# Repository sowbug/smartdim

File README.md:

SmartDim
===

A timed dimmer for the Ikea JANSJÖ lamp. Using pulse-width modulation, it starts the light at full brightness, waits 30 minutes, then dims gradually to full darkness over 5 minutes. In theory it's good for a kid who wakes up when the parent comes back in to shut off the reading light.

Parts List
===

* One [Ikea JANSJÖ clip lamp](http://www.ikea.com/us/en/catalog/products/30237256/#/20315674). The one I got was item 801.696.36 and it was marked down to $12.99. If it has a 2-pin DIN speaker connector for the power adapter, and the power is 4 volts at 0.75 amps (3 watts), then it ought to work with this project. Be careful and check the voltage. I've seen other lamps in the JANSJÖ series that run on 7 volts, and that voltage will kill this circuit.
* A way to manufacture PCBs. You will, of course, use [OSH Park](https://oshpark.com/).
* Any old N-channel MOSFET in SOT-223 package that can handle a couple of amps. I used the [NDT3055L](https://www.jameco.com/webapp/wcs/stores/servlet/Product_10001_10001_874875_-1), which says it can dissipate 3 watts. I'd have preferred something with more margin for error, but this was available at Jameco will-call.
* An ATTiny85-20SU, which is the SOIC-8 package. Depending on how lazy you are, you can pick a smaller version of this series and figure out how to scrunch down the firmware size.
* A 6-pin AVR ISP.
* Either a [ProtoProg](http://protofusion.org/wordpress/2013/05/open-hardware-pogo-pin-programmer/) connector or an SOIC-8 clip to program the t85. Yeah, I probably could have fit a standard 6-pin header on this board. Sorry about that.
* An 0805 1uF capacitor.
* The standard [Dangerous Prototypes octagon-shaped SMD button](http://dangerousprototypes.com/docs/Partlist#Buttons_and_switches) (ALPS SKQGAKE010) (note the KE010 variant, which has a 3.43N rather than 2.55N operating force, but which is 50 cents cheaper). I usually use the [TD-85XU](http://www.dx.com/p/td-85xu-mini-tact-switches-50-piece-pack-122514#.VmRq-H4rKV4) because you can acquire a lifetime supply for $10, but I wanted something that was easier to find in the dark, and I happened to have some left over from another project. Looking back (to a few hours ago when this project started), I probably should have picked something a little less premium and with even more travel ([take your pick](http://www.dx.com/s/tact+switch)).
* Depending on whether you want to cut the lamp wires, a male and female pair of 2-pin DIN speaker connectors. You can find these on eBay.

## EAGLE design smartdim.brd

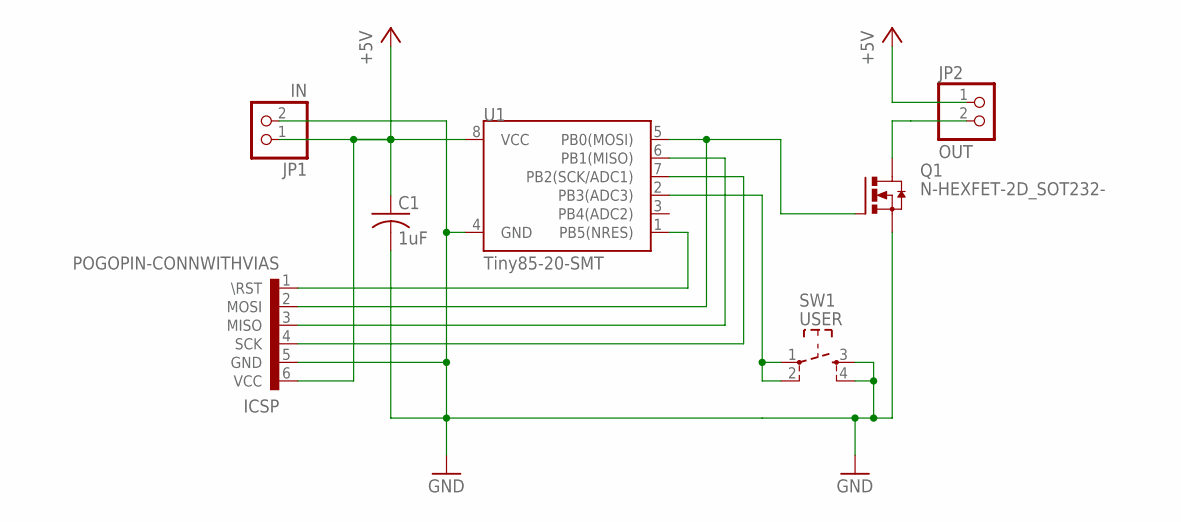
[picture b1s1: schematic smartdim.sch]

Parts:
C1: 1uF; C0805
ICSP: POGOPIN-CONNWITHVIAS; POGOPROG-CONN-0H
JP1: IN; 1X02
JP2: OUT; 1X02
Q1: N-HEXFET-2D_SOT232-; SOT223
SW1: USER; SW_TACT_SMALL
U1: Tiny85-20-SMT; SO08-EIAJ

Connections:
+5V: C1.1, ICSP.6 (VCC), JP1.1, JP2.1, U1.8 (VCC)
GND: C1.2, ICSP.5 (GND), JP1.2, Q1.3 (S), SW1.3, SW1.4, U1.4 (GND)
MISO: ICSP.3 (MISO), U1.6 (PB1(MISO))
MOSI/PWM: ICSP.2 (MOSI), Q1.1 (G), U1.5 (PB0(MOSI))
NRES: ICSP.1 (\RST), U1.1 (PB5(NRES))
PWM_VSS: JP2.2, Q1.2 (D), Q1.4 (D)
SCK: ICSP.4 (SCK), U1.7 (PB2(SCK/ADC1))
USER_INPUT: SW1.1, SW1.2, U1.2 (PB3(ADC3))

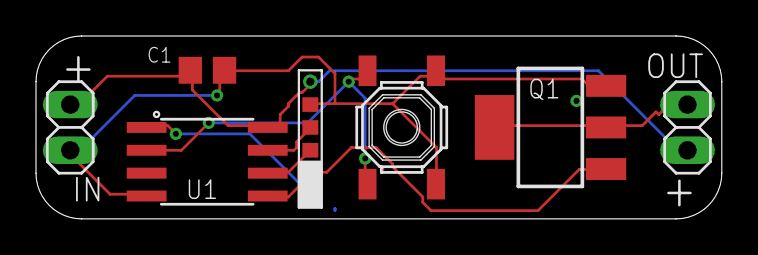
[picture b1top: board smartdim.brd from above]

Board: 2 copper layers, 38.1 x 10.2 mm, 7 parts (0 on the bottom side), 8 nets.

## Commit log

2015-12-06 New.
2015-12-06 Rename
2015-12-06 Remove unnecessary pullup
2015-12-06 Easier to read labels
2015-12-06 Add silkscreen label
2015-12-06 osh-1
2015-12-06 New sample sketch
2015-12-06 More docs
2015-12-06 Saved 50 cents on parts
2015-12-22 osh-2: fix swapped MOSFET drain/source
2016-01-03 IN/OUT were in wrong layer. Fixed

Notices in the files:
parts and their libraries:
SparkFun-DigitalIC: Licensing: Creative Commons ShareAlike 4.0 International - https://creativecommons.org/licenses/by-sa/4.0
